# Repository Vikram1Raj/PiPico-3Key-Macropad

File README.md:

# PiPico-3Key-Macropad 

A 3-Key Macropad with an EC-11 rotary encoder.(**Case Not Included**)

This project is interfaced with a [Raspberry Pi Pico](https://www.raspberrypi.com/documentation/microcontrollers/raspberry-pi-pico.html) along with [CircuitPython](https://circuitpython.org/) and [KMK Firmware](https://github.com/KMKfw/kmk_firmware)

### Components:
1. Raspberry Pi Pico - 1
2. EC-11(switch type) Rotary Encoder - 1
3. 1N4148 Zener Diodes - 4
4. MX Keyswitches - 3

## Project Details:
* This repository includes the Schematic File, PCB file, and Gerber Files.
* The Rotary encoder has been configured to be used as a Volume control knob and the button to mute.
* The 3 key switches have been mapped to Z, X and C.
* The [boot.py](boot.py) file is included to ensure the keypad is not detected as a drive every time.
* Hold down the "Z" key when connecting the keypad to your device again to use the Pico as a drive again.

## Final Look:

### 3D Render:

### Future Changes(ETA : Dunno):
* Make a 3d Printed Case for the PCB

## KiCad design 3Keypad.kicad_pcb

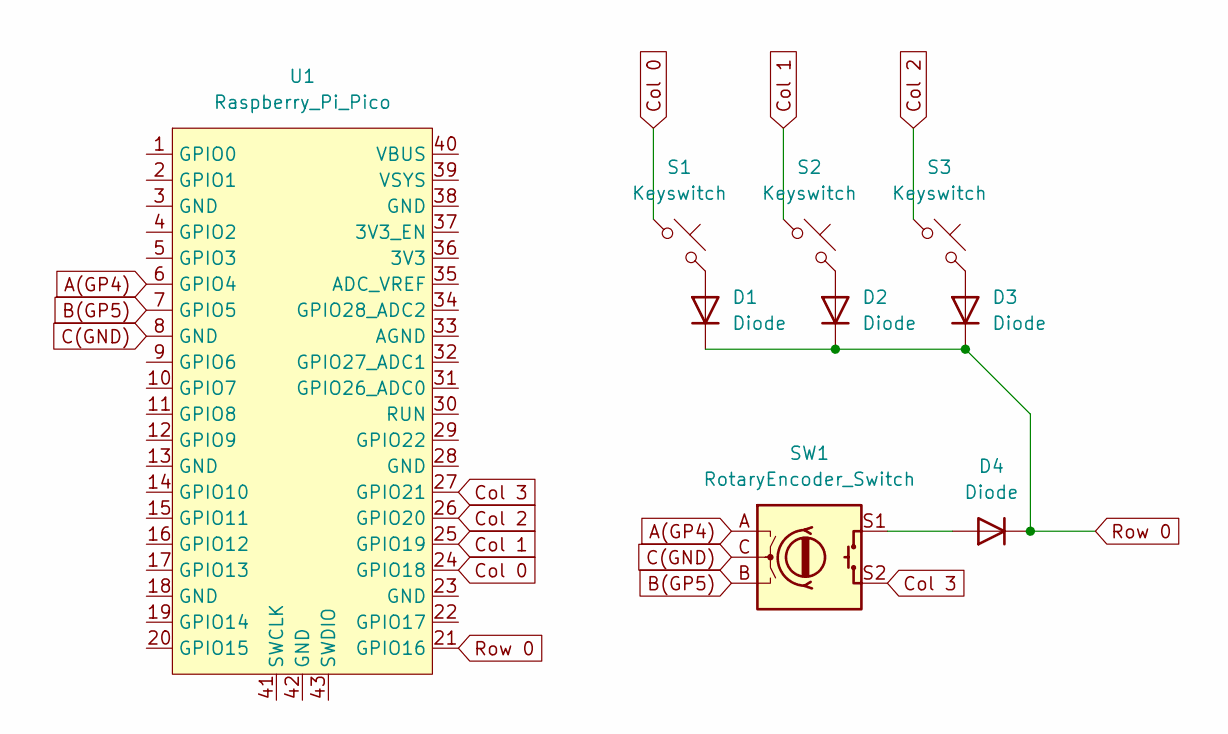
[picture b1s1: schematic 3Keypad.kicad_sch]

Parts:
D1, D2, D3, D4: Diode; Diode_DO-35
S1, S2, S3: Keyswitch; MX_PCB_1.00u
SW1: RotaryEncoder_Switch; RotaryEncoder_Alps_EC11E-Switch_Vertical_H20mm
U1: Raspberry_Pi_Pico

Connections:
A(GP4): SW1.A, U1.6 (GPIO4)
B(GP5): SW1.B, U1.7 (GPIO5)
C(GND): SW1.C, U1.8 (GND)
Col 0: S1.1, U1.24 (GPIO18)
Col 1: S2.1, U1.25 (GPIO19)
Col 2: S3.1, U1.26 (GPIO20)
Col 3: SW1.S2, U1.27 (GPIO21)
unnamed: D1.2 (A), S1.2
unnamed: D2.2 (A), S2.2
unnamed: D3.2 (A), S3.2
unnamed: D4.2 (A), SW1.S1
Row 0: D1.1 (K), D2.1 (K), D3.1 (K), D4.1 (K), U1.21 (GPIO16)

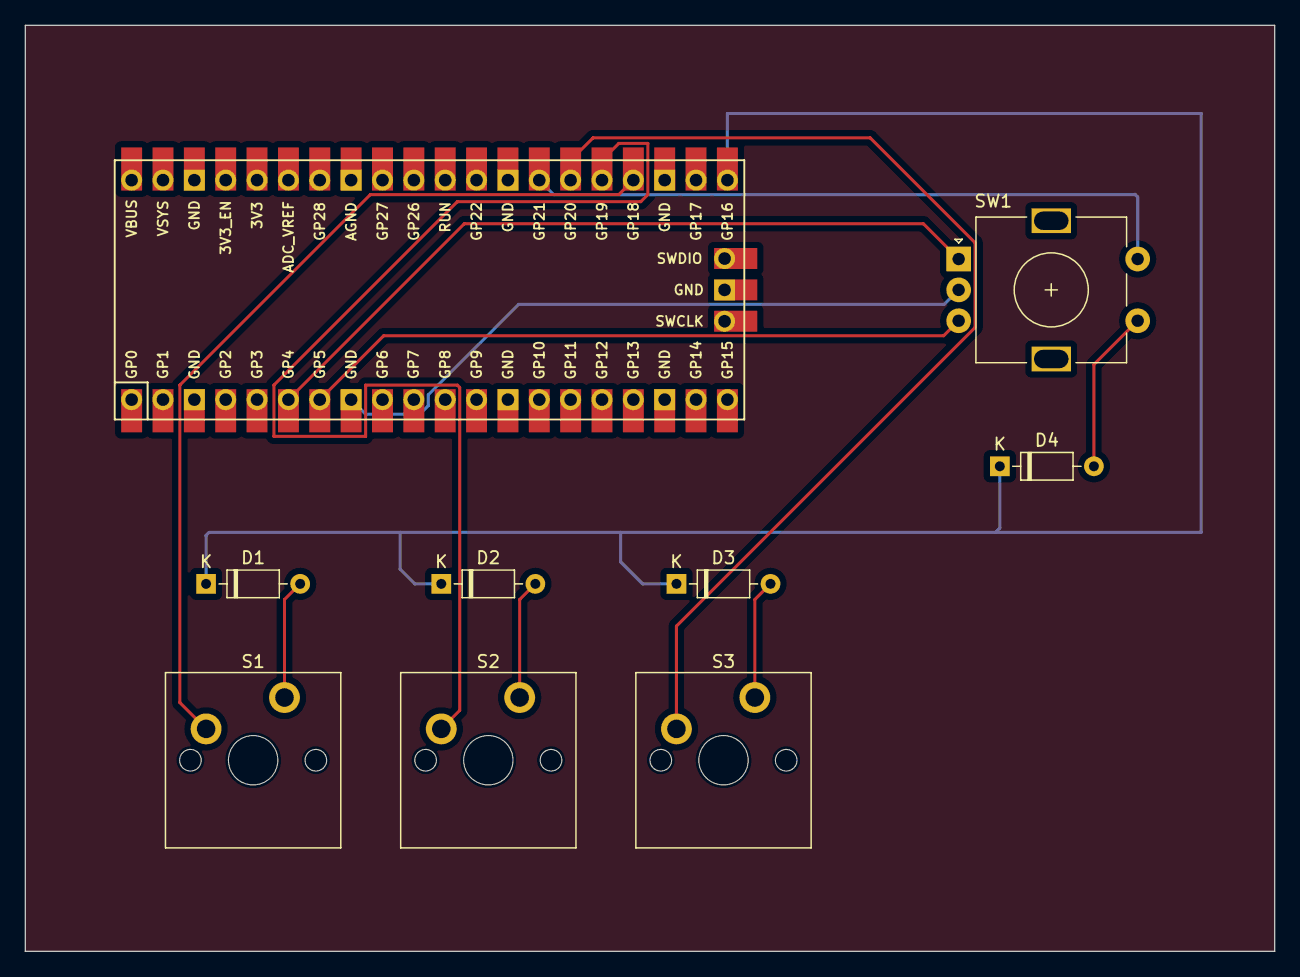
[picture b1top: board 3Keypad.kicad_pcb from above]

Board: 2 copper layers, 101.2 x 75.0 mm, 9 parts (0 on the bottom side), 12 nets.

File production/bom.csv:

Designator,Footprint,Quantity,Value,LCSC Part #
"D1, D2, D3, D4",Diode_DO-35,4,Diode,
"S1, S2, S3",MX_PCB_1.00u,3,Keyswitch,
SW1,RotaryEncoder_Alps_EC11E-Switch_Vertical_H20mm,1,RotaryEncoder_Switch,
U1,Raspberry_Pi_Pico,1,Raspberry_Pi_Pico,

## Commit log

2024-01-23 First Commit of this Project
2024-01-23 Added a Readme file in local repo
2024-01-23 Removed unnecessary libs
2025-02-03 Update README.md
    KMK Firmware Link update
